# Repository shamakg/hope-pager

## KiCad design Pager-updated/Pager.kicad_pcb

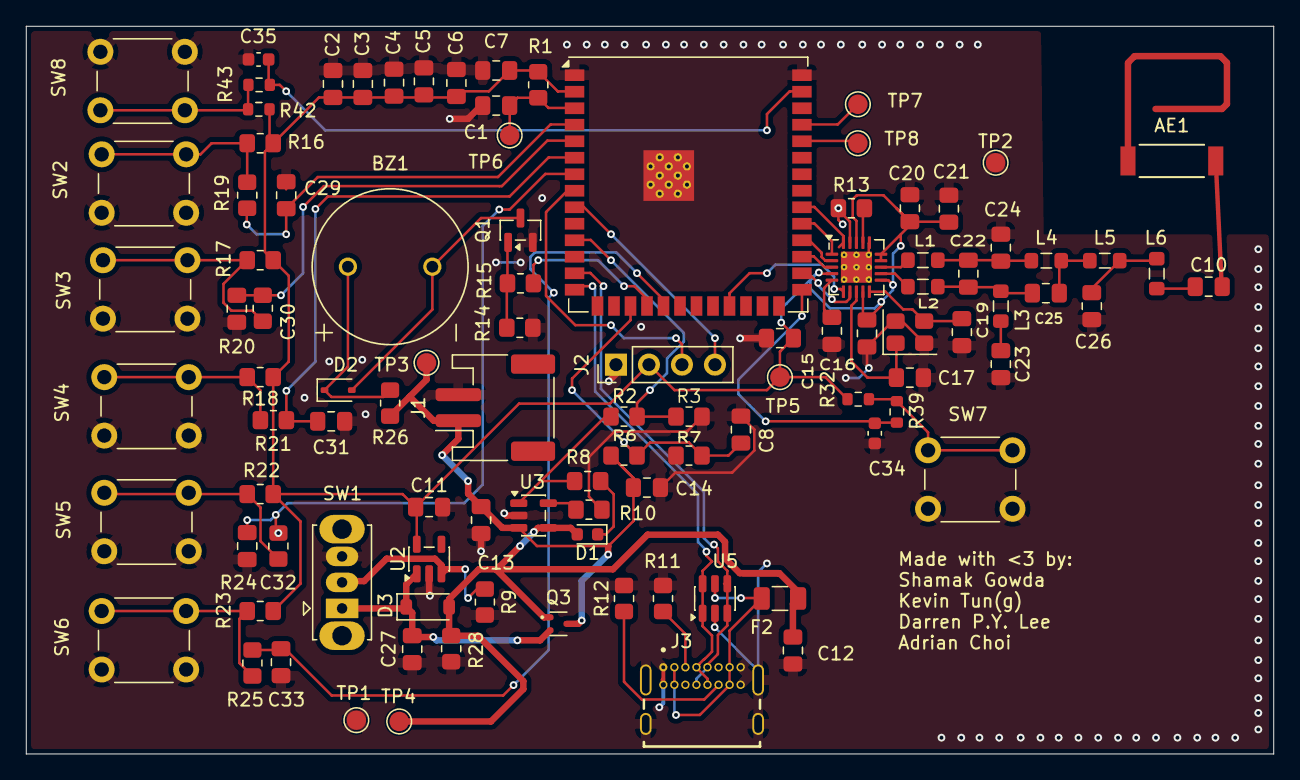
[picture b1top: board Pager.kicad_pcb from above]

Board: 2 copper layers, 96.0 x 56.0 mm, 101 parts (0 on the bottom side), 58 nets.

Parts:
AE1: Antenna; ANT_0915AT43A0026E_JOT
BZ1: Buzzer; XDCR_AT-1220-TT-R
C1: 1uF; C_0805_2012Metric_Pad1.18x1.45mm_HandSolder
C2: 10nF; C_0805_2012Metric_Pad1.18x1.45mm_HandSolder
C3, C4, C5, C6, C8, C15, C18, C20, C21, C29, C30, C31, C32, C33: 100nF; C_0805_2012Metric_Pad1.18x1.45mm_HandSolder
C7: 22uF; C_0805_2012Metric_Pad1.18x1.45mm_HandSolder
C10: 12pF; C_0805_2012Metric_Pad1.18x1.45mm_HandSolder
C11: 10uF; C_0805_2012Metric_Pad1.18x1.45mm_HandSolder
C12, C13, C14: 4.7uF; C_0805_2012Metric_Pad1.18x1.45mm_HandSolder
C16: 100 nF; C_0805_2012Metric_Pad1.18x1.45mm_HandSolder
C17, C19: 15 pF; C_0805_2012Metric_Pad1.18x1.45mm_HandSolder
C22: 1.0 pF; C_0805_2012Metric_Pad1.18x1.45mm_HandSolder
C23: 100 pF; C_0805_2012Metric_Pad1.18x1.45mm_HandSolder
C24, C25: 1.5 pF; C_0805_2012Metric_Pad1.18x1.45mm_HandSolder
C26: 3.3 pF; C_0805_2012Metric_Pad1.18x1.45mm_HandSolder
C27: 1 µF; C_0805_2012Metric_Pad1.18x1.45mm_HandSolder
C34, C35: 100nF; C_0603_1608Metric
D1: LED; LED_0603_1608Metric
D2: 1N4148WS; D_SOD-323
D3: D_Schottky; D_SOD-123
F2: Polyfuse_Small; Fuse_1206_3216Metric
J1: Conn_01x02_Pin; JST_PH_S2B-PH-SM4-TB_1x02-1MP_P2.00mm_Horizontal
J2: Conn_01x04; PinHeader_1x04_P2.54mm_Vertical
J3: USB4085-GF-A_REVB; GCT_USB4085-GF-A_REVB
L1, L2, L5, L6: 12 nH; L_0805_2012Metric_Pad1.05x1.20mm_HandSolder
L3, L4: 18 nH; L_0805_2012Metric_Pad1.05x1.20mm_HandSolder
Q1: AO3400A; SOT-23
Q3: Q_PMOS_GSD; SOT-523
R1, R2, R16, R17, R18, R22, R23: 10k; R_0805_2012Metric_Pad1.20x1.40mm_HandSolder
R3: 18k; R_0805_2012Metric_Pad1.20x1.40mm_HandSolder
R6, R9, R14, R28: 100k; R_0805_2012Metric_Pad1.20x1.40mm_HandSolder
R7: 180k; R_0805_2012Metric_Pad1.20x1.40mm_HandSolder
R8: 470; R_0805_2012Metric_Pad1.20x1.40mm_HandSolder
R10: 2.49k; R_0805_2012Metric_Pad1.20x1.40mm_HandSolder
R11, R12: 5.1k; R_0805_2012Metric_Pad1.20x1.40mm_HandSolder
R13: 56 kΩ; R_0805_2012Metric_Pad1.20x1.40mm_HandSolder
R15: 100; R_0805_2012Metric_Pad1.20x1.40mm_HandSolder
R19, R20, R21, R24, R25: 1k; R_0805_2012Metric_Pad1.20x1.40mm_HandSolder
R26: 47; R_0805_2012Metric_Pad1.20x1.40mm_HandSolder
R32, R42: 10k; R_0603_1608Metric
R39, R43: 1k; R_0603_1608Metric
SW1: SW_SPDT; SW_Slide_SPDT_Straight_CK_OS102011MS2Q
SW2, SW3, SW4, SW5, SW6, SW7, SW8: SW_Push; SW_PUSH_6mm
TP1, TP2, TP3, TP4, TP5, TP6, TP7, TP8: TestPoint; TestPoint_Pad_D1.5mm
U2: AP2112K-3.3; SOT-23-5
U3: MCP73831-2-OT; SOT-23-5
U4: CC1101RGPR; Texas_RGP0020H_VQFN-20-1EP_4x4mm_P0.5mm_EP2.4x2.4mm_Thermal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
U5: USBLC6-2SC6; SOT-23-6
U6: ESP32-S3-WROOM-1; ESP32-S3-WROOM-1U
Y1: 26 MHz; Crystal_SMD_3225-4Pin_3.2x2.5mm

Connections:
+3V3: C2.1, C3.1, C4.1, C5.1, C6.1, C7.1, C11.1, C15.1, C18.1, C20.2, C21.1, J2.2, R1.1, R16.1, R17.1, R18.1, R22.1, R23.1, R32.1, R42.1, TP5.1 (1_1), U2.5 (VOUT), U4.4 (DVDD), U4.9 (AVDD), U4.11 (AVDD), U4.14 (AVDD), U4.15 (AVDD), U4.18 (DGUARD), U6.2 (3V3)
/Batt_Sense+: C8.2, R6.2, R7.2, U6.17 (IO9)
/Button_6: C34.1, R39.2, U6.27 (IO0)
/Button_7: C35.1, R43.2, U6.39 (IO1)
/Buttons/Button_1: C29.1, R19.2, U6.4 (IO4)
/Buttons/Button_2: C30.1, R20.2, U6.5 (IO5)
/Buttons/Button_3: C31.1, R21.2, U6.6 (IO6)
/Buttons/Button_4: C32.1, R24.2, U6.7 (IO7)
/Buttons/Button_5: C33.1, R25.2, U6.19 (IO11)
/Buzzer_PWM: R15.2, U6.18 (IO10)
/Charging: R2.1, R8.2, U3.1 (STAT)
/Display/SCK: J2.3, U6.8 (IO15)
/Display/SDA: J2.4, U6.9 (IO16)
/ESP_EN: C1.1, R1.2, TP6.1 (1_1), U6.3 (EN)
/Power/EN: R9.1, SW1.2 (B), U2.3 (EN)
/Power/USBD+: J3.A6 (DP1), J3.B6 (DP2), U5.1 (I/O1), U5.6 (I/O1), U6.14 (USB_D+)
/Power/USBD-: J3.A7 (DN1), J3.B7 (DN2), U5.3 (I/O2), U5.4 (I/O2), U6.13 (USB_D-)
/RF_CSn: U4.7 (CSn), U6.28 (IO35)
/RF_GDO0: U4.6 (GDO0), U6.23 (IO21)
/RF_GDO2: U4.3 (GDO2), U6.29 (IO36)
/RF_SCLK: U4.1 (SCLK), U6.31 (IO38)
/RF_SI: U4.20 (SI), U6.32 (IO39)
/RF_SO: U4.2 (SO_(GDO1)), U6.30 (IO37)
/RXD0: TP8.1 (1_1), U6.36 (RXD0)
/TXD0: TP7.1 (1_1), U6.37 (TXD0)
GND: C1.2, C2.2, C3.2, C4.2, C5.2, C6.2, C7.2, C8.1, C11.2, C12.1, C13.1, C14.1, C15.2, C16.2, C17.2, C18.2, C19.2, C20.1, C21.2, C23.2, C24.2, C26.1, C27.2, C29.2, C30.2, C31.2, C32.2, C33.2, C34.2, C35.2, J1.2, J2.1, J3.A1 (GND), J3.A12 (GND__1), J3.B1 (GND__2), J3.B12 (GND__3), J3.S1 (SHELL), J3.S2 (SHELL__1), J3.S3 (SHELL__2), J3.S4 (SHELL__3), Q1.2 (S), R3.2, R7.1, R9.2, R10.1, R11.2, R12.2, R13.2, R14.2, R28.2, SW1.3 (C), SW2.2, SW3.2, SW4.2, SW5.2, SW6.2, SW7.2, SW8.2, TP1.1 (1_1), TP2.1 (1_1), U2.2 (GND), U3.2 (V_{SS}), U4.16 (GND), U4.19 (GND), U4.21 (EP_GND), U5.2 (GND), U6.1 (GND), U6.40 (GND), U6.41 (GND), Y1.2 (G), Y1.4 (G)
unnamed: AE1.1 (A_1), C10.2
unnamed: BZ1.1 (+), D2.1 (K), R26.2
unnamed: BZ1.2 (-), D2.2 (A), Q1.3 (D)
unnamed: C10.1, L6.1
unnamed: C22.1, C24.1, L1.1, L4.2
unnamed: C22.2, C25.1, L2.1, L3.2
unnamed: C23.1, L3.1
unnamed: C25.2, L4.1, L5.2
unnamed: C26.2, L5.1, L6.2
unnamed: D1.1 (K), R8.1
unnamed: J3.A5 (CC1), R11.1
unnamed: J3.B5 (CC2), R12.1
unnamed: F2.2, J3.A4 (VBUS), J3.A9 (VBUS__1), J3.B4 (VBUS__2), J3.B9 (VBUS__3), U5.5 (VBUS)
unnamed: Q1.1 (G), R14.1, R15.1
unnamed: R16.2, R19.1, SW2.1
unnamed: R17.2, R20.1, SW3.1
unnamed: R18.2, R21.1, SW4.1
unnamed: R22.2, R24.1, SW5.1
unnamed: R23.2, R25.1, SW6.1
unnamed: R32.2, R39.1, SW7.1
unnamed: R42.2, R43.1, SW8.1
unnamed: R10.2, U3.5 (PROG)
unnamed: C16.1, U4.5 (DCOUPL)
unnamed: R13.1, U4.17 (RBIAS)
unnamed: L1.2, U4.13 (RF_N)
unnamed: L2.2, U4.12 (RF_P)
unnamed: C17.1, U4.8 (XOSC_Q1), Y1.1
unnamed: C19.1, U4.10 (XOSC_Q2), Y1.3
unnamed: R2.2, R3.1, U6.11 (IO18)
V_{BATT}: C13.2, C14.2, J1.1, Q3.3 (D), R6.1, R26.1, TP3.1 (1_1), U3.3 (V_{BAT})
V_{LDO}: C27.1, D3.1 (K), Q3.2 (S), SW1.1 (A), U2.1 (VIN)
V_{SYS}: C12.2, D1.2 (A), D3.2 (A), F2.1, Q3.1 (G), R28.1, TP4.1 (1_1), U3.4 (V_{DD})
